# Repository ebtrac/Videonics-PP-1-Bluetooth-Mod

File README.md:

# Videonics-PP-1-Bluetooth-Mod
 KiCad 6.0 Project Files for the Videonics Processor Plus and modifications for adding bluetooth control  
- [Schematics](ebtrac_mod_pp1.pdf)
- [Firmware](https://github.com/ebtrac/pp1_esp32_control)

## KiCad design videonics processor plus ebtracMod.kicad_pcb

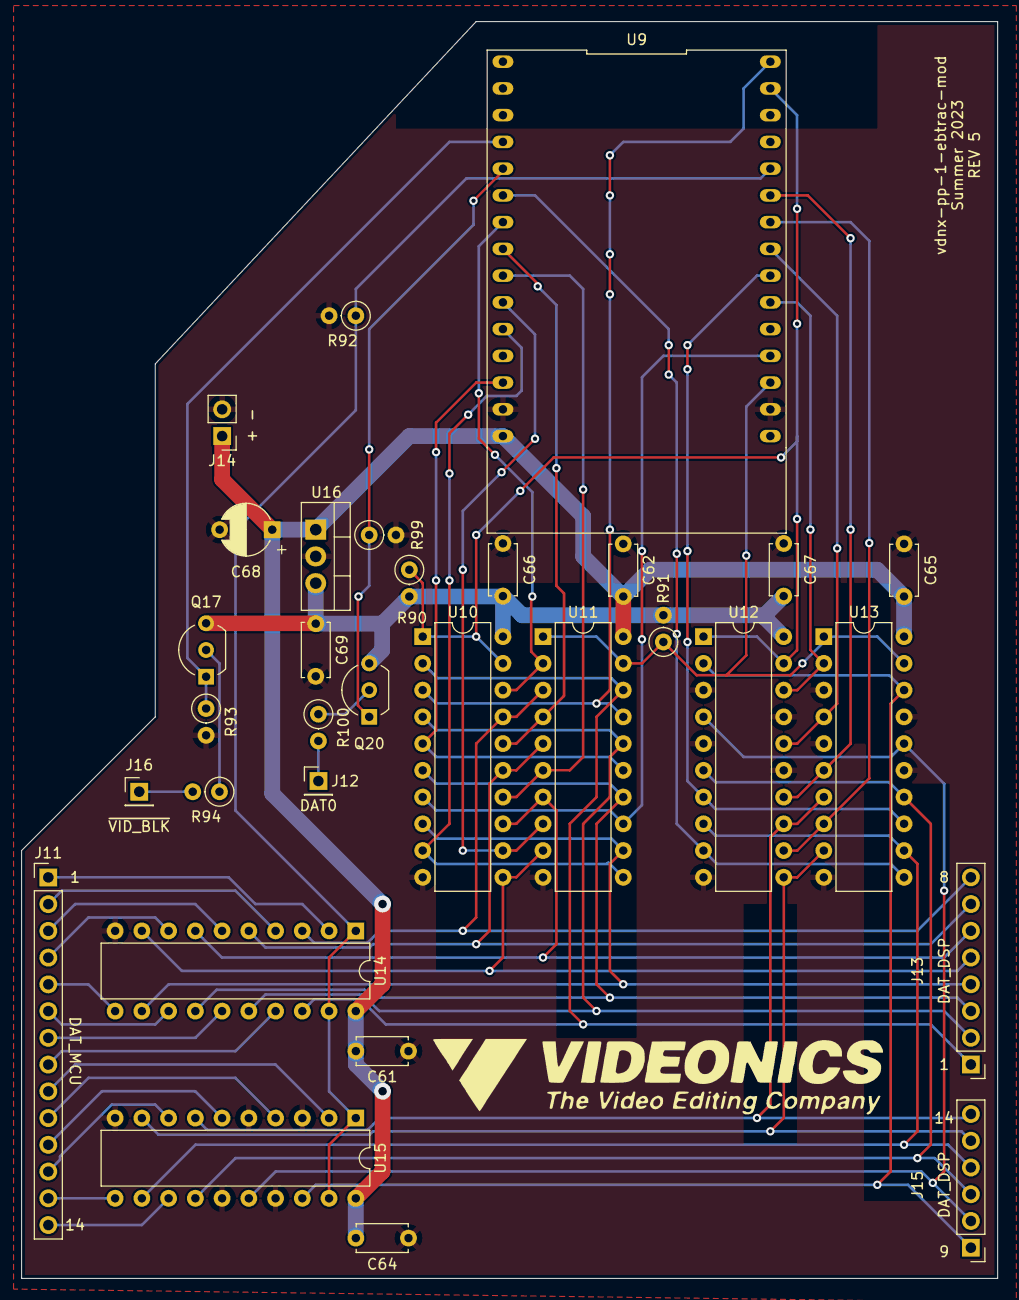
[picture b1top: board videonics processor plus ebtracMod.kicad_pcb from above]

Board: 2 copper layers, 92.7 x 119.4 mm, 31 parts (0 on the bottom side), 54 nets.

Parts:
C61, C62, C64, C65, C66, C67: 100nF; C_Disc_D4.7mm_W2.5mm_P5.00mm
C68: 4.7uF; CP_Radial_D8.0mm_P5.00mm
C69: 1uF; C_Disc_D5.0mm_W2.5mm_P5.00mm
J11: DAT_MCU; PinHeader_1x14_P2.54mm_Vertical
J12: DAT0; PinHeader_1x01_P2.54mm_Vertical
J13: DAT_DSP_1..8; PinHeader_1x08_P2.54mm_Vertical
J14: + -; PinHeader_1x02_P2.54mm_Vertical
J15: DAT_DSP_9..14; PinHeader_1x06_P2.54mm_Vertical
J16: ~{VID_BLK}; PinHeader_1x01_P2.54mm_Vertical
Q17, Q20: 2N3904; TO-92_Inline_Wide
R90, R91, R92, R93, R99: 10k; R_Axial_DIN0207_L6.3mm_D2.5mm_P2.54mm_Vertical
R94, R100: 220k; R_Axial_DIN0207_L6.3mm_D2.5mm_P2.54mm_Vertical
U9: BAEASU_ESP32_DevKit_v1; DIP-30_1000_ELL
U10, U11, U12, U13, U14, U15: 74LS244; DIP-20_W7.62mm
U16: MCP1826S-3302E/AB; TO-220-3_Vertical

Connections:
+3.3V: C66.1, C67.1, C69.1, Q17.3 (C), Q20.3 (C), R90.2, R91.2, U10.20 (VCC), U12.20 (VCC), U16.3 (VO)
+5V: C61.1, C62.1, C64.1, C65.1, C68.1, J14.1, U9.15 (VIN), U11.20 (VCC), U13.20 (VCC), U14.20 (VCC), U15.20 (VCC), U16.1 (VI)
/DAT Bus Buffer/DAT_DSP1: J13.1, U10.2 (I0a), U11.18 (O0a), U14.18 (O0a)
/DAT Bus Buffer/DAT_DSP2: J13.2, U10.4 (I1a), U11.16 (O1a), U14.16 (O1a)
/DAT Bus Buffer/DAT_DSP3: J13.3, U10.6 (I2a), U11.14 (O2a), U14.14 (O2a)
/DAT Bus Buffer/DAT_DSP4: J13.4, U10.8 (I3a), U11.12 (O3a), U14.12 (O3a)
/DAT Bus Buffer/DAT_DSP5: J13.5, U10.11 (I0b), U11.9 (O0b), U14.9 (O0b)
/DAT Bus Buffer/DAT_DSP6: J13.6, U10.13 (I1b), U11.7 (O1b), U14.7 (O1b)
/DAT Bus Buffer/DAT_DSP7: J13.7, U10.15 (I2b), U11.5 (O2b), U14.5 (O2b)
/DAT Bus Buffer/DAT_DSP8: J13.8, U10.17 (I3b), U11.3 (O3b), U14.3 (O3b)
/DAT Bus Buffer/DAT_DSP9: J15.1, U12.2 (I0a), U13.18 (O0a), U15.18 (O0a)
/DAT Bus Buffer/DAT_DSP10: J15.2, U12.4 (I1a), U13.16 (O1a), U15.16 (O1a)
/DAT Bus Buffer/DAT_DSP11: J15.3, U12.6 (I2a), U13.14 (O2a), U15.14 (O2a)
/DAT Bus Buffer/DAT_DSP12: J15.4, U12.8 (I3a), U13.12 (O3a), U15.12 (O3a)
/DAT Bus Buffer/DAT_DSP13: J15.5, U12.11 (I0b), U13.9 (O0b), U15.9 (O0b)
/DAT Bus Buffer/DAT_DSP14: J15.6, U12.13 (I1b), U13.7 (O1b), U15.7 (O1b)
/DAT Bus Buffer/DAT_MCU1: J11.1, U14.2 (I0a)
/DAT Bus Buffer/DAT_MCU2: J11.2, U14.4 (I1a)
/DAT Bus Buffer/DAT_MCU3: J11.3, U14.6 (I2a)
/DAT Bus Buffer/DAT_MCU4: J11.4, U14.8 (I3a)
/DAT Bus Buffer/DAT_MCU5: J11.5, U14.11 (I0b)
/DAT Bus Buffer/DAT_MCU6: J11.6, U14.13 (I1b)
/DAT Bus Buffer/DAT_MCU7: J11.7, U14.15 (I2b)
/DAT Bus Buffer/DAT_MCU8: J11.8, U14.17 (I3b)
/DAT Bus Buffer/DAT_MCU9: J11.9, U15.2 (I0a)
/DAT Bus Buffer/DAT_MCU10: J11.10, U15.4 (I1a)
/DAT Bus Buffer/DAT_MCU11: J11.11, U15.6 (I2a)
/DAT Bus Buffer/DAT_MCU12: J11.12, U15.8 (I3a)
/DAT Bus Buffer/DAT_MCU13: J11.13, U15.11 (I0b)
/DAT Bus Buffer/DAT_MCU14: J11.14, U15.13 (I1b)
/ESP32/DAT_DSP0: J12.1, R100.2
/ESP32/DAT_ESP0: Q20.1 (E), R99.1, U9.5 (D35)
/ESP32/DAT_ESP1: U9.7 (D33), U10.18 (O0a), U11.2 (I0a)
/ESP32/DAT_ESP2: U9.8 (D25), U10.16 (O1a), U11.4 (I1a)
/ESP32/DAT_ESP3: U9.9 (D26), U10.14 (O2a), U11.6 (I2a)
/ESP32/DAT_ESP4: U9.10 (D27), U10.12 (O3a), U11.8 (I3a)
/ESP32/DAT_ESP5: U9.11 (D14), U10.9 (O0b), U11.11 (I0b)
/ESP32/DAT_ESP6: U9.19 (D2), U10.7 (O1b), U11.13 (I1b)
/ESP32/DAT_ESP7: U9.13 (D13), U10.5 (O2b), U11.15 (I2b)
/ESP32/DAT_ESP8: U9.30 (D23), U10.3 (O3b), U11.17 (I3b)
/ESP32/DAT_ESP9: U9.21 (RX2), U12.18 (O0a), U13.2 (I0a)
/ESP32/DAT_ESP10: U9.23 (D5), U12.16 (O1a), U13.4 (I1a)
/ESP32/DAT_ESP11: U9.25 (D19), U12.14 (O2a), U13.6 (I2a)
/ESP32/DAT_ESP12: U9.24 (D18), U12.12 (O3a), U13.8 (I3a)
/ESP32/DAT_ESP13: U9.6 (D32), U12.9 (O0b), U13.11 (I0b)
/ESP32/DAT_ESP14: U9.22 (TX2), U12.7 (O1b), U13.13 (I1b)
/ESP32/ESP_VID_BLK: Q17.1 (E), R93.1, U9.4 (D34)
/ESP32/~BUF_OE: R92.1, U9.26 (D21), U14.1 (OEa), U14.19 (OEb), U15.1 (OEa), U15.19 (OEb)
/ESP32/~HIJACK: R91.1, U9.18 (D15), U11.1 (OEa), U11.19 (OEb), U13.1 (OEa), U13.19 (OEb)
/ESP32/~LISTEN: R90.1, U9.29 (D22), U10.1 (OEa), U10.19 (OEb), U12.1 (OEa), U12.19 (OEb)
/ESP32/~VID_BLK: J16.1, R94.2
GND: C61.2, C62.2, C64.2, C65.2, C66.2, C67.2, C68.2, C69.2, J14.2, R92.2, R93.2, R99.2, U9.14 (GND), U9.17 (GND), U10.10 (GND), U11.10 (GND), U12.3 (O3b), U12.5 (O2b), U12.10 (GND), U12.15 (I2b), U12.17 (I3b), U13.3 (O3b), U13.5 (O2b), U13.10 (GND), U13.15 (I2b), U13.17 (I3b), U14.10 (GND), U15.3 (O3b), U15.5 (O2b), U15.10 (GND), U15.15 (I2b), U15.17 (I3b), U16.2 (GND)
unnamed: Q17.2 (B), R94.1
unnamed: Q20.2 (B), R100.1

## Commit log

2023-07-08 Initial Design
    Problem: Level shifters need to be completely redesigned.
2023-07-08 Redesigned Level Shifting Schematic
2023-07-08 Changed level shifter inverter supply from 5V to 3.3V
2023-07-17 Minor formatting updates
2023-07-17 update footprints
2023-07-18 smaller resistor footprint
2023-07-20 PCB Redesign Finished
2023-07-20 Add some labels and gerber files
2023-07-21 misc updates
2023-07-23 cleanup and rename subsheets, increment rev
2023-07-23 added bom exclusions for non mod components
2023-07-23 add bom with cost analysis
2023-07-23 updated cost
2023-07-23 added hyperlinks
2023-07-23 added schematics
2023-07-23 added rev 4 gerbers
2023-07-27 schematic updated
2023-07-27 assigned footprints
2023-07-27 add 3.3V 1A regulator
2023-07-27 PCB rev 5
2023-07-28 added vid_blk and fixed inverter on dat 0
2023-07-28 update gerbers
2023-07-28 import heirarchical pin
2023-09-30 Add Rev 5 schematic and update readme
